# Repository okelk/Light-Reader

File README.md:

# Light-Reader

Light Reader is a simple physical interface to trigger sound with light. Device consists of a mechanical part that allows light control with perforated discs, and an electronic part, an integrated circuit that generates sound according to the light signal duration and intensity.

Project further developed at PifCamp 2020 http://pif.camp/ by Saša Spačal https://www.agapea.si/en/. Stripboard-Layout by Klemens Kohlweis.

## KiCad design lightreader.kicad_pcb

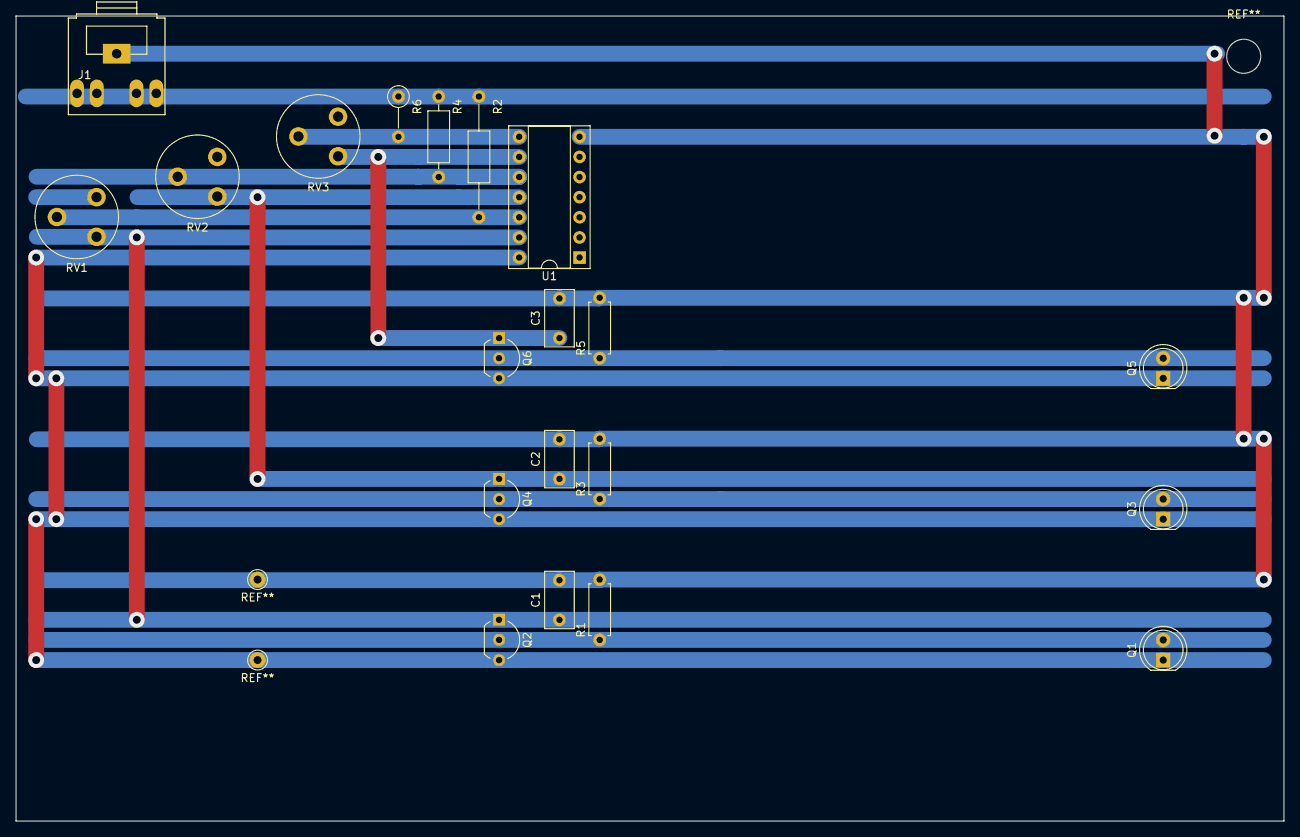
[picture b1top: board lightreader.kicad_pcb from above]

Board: 2 copper layers, 160.0 x 101.6 mm, 20 parts (0 on the bottom side), 12 nets.

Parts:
C1, C2, C3: C; C_Rect_L7.0mm_W3.5mm_P5.00mm
J1: AudioJack3; Tayda_3.5mm_stereo_TRS_jack_A-853
Q1, Q3, Q5: Q_Photo_NPN; LED_D5.0mm
Q2, Q4, Q6: BC557; TO-92_Inline_Wide
R1, R3, R5: 4K7; R_Axial_DIN0207_L6.3mm_D2.5mm_P7.62mm_Horizontal
R2: 10K; R_Axial_DIN0207_L6.3mm_D2.5mm_P15.24mm_Horizontal
R4: 10K; R_Axial_DIN0207_L6.3mm_D2.5mm_P10.16mm_Horizontal
R6: 10K; R_Axial_DIN0207_L6.3mm_D2.5mm_P5.08mm_Vertical
RV1, RV2, RV3: R_POT; Potentiometer_Piher_PT-10-V05_Vertical
U1: 40106; DIP-14_W7.62mm_Socket

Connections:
+9V: Q1.1, Q2.3, Q3.1, Q4.3, Q5.1, Q6.3, U1.14
GND: C1.2, C2.2, C3.2, J1.1, R1.2, R3.2, R5.2, U1.7
unnamed: C1.1, Q2.1, RV1.3, U1.13
unnamed: C2.1, Q4.1, RV2.3, U1.11
unnamed: C3.1, Q6.1, RV3.3, U1.9
unnamed: J1.2, J1.3, J1.4, J1.5, R2.1, R4.1, R6.1
unnamed: Q1.2, Q2.2, R1.1
unnamed: Q3.2, Q4.2, R3.1
unnamed: Q5.2, Q6.2, R5.1
unnamed: R2.2, RV1.2, U1.12
unnamed: R4.2, RV2.2, U1.10
unnamed: R6.2, RV3.2, U1.8

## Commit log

2020-08-08 move img
